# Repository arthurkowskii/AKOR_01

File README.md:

# AKOR_01

AKOR_01 is a compact hardware controller for playing notes, chords, and simple sequences.

These renders show the current NO_LED PCB revision: the RGB subsystem is absent, the matrix and encoder controls are routed, and the diode matrix is on the solder side.

The confirmed V0 interface contains a 4 × 5 performance grid plus Shift (21 MX switches total), seven push encoders, and an OLED display.

## Architecture locked on 2026-07-31

**V0 is an independent USB-MIDI controller based on Raspberry Pi Pico 2 H.**

A future standalone synthesizer is a separate V2 project. V2 is intentionally not a compatibility constraint for the V0 PCB.

### V0 hardware target

- Raspberry Pi Pico 2 H as the USB-MIDI device and control processor;
- 21 MX-compatible switches and 21 × 1N4148 in a scanned matrix;
- 7 bare EC11-style encoders with integrated push switches;
- 1 × MCP23017 I²C GPIO expander;
- 1 × SSD1306-compatible I²C OLED module;
- no onboard audio or DSP output stage.

The intended signal allocation is:

- encoder `A/B`: 14 direct Pico GPIO inputs;
- one encoder push switch: one direct Pico GPIO input;
- matrix rows/columns plus six encoder push switches: one MCP23017;
- OLED and MCP23017: shared 3.3 V I²C bus;
- USB: Pico 2 H onboard micro-USB, carrying power and class-compliant MIDI.

## Software state

The existing C++ prototype can:

- generate sine, square, triangle, and sawtooth waveforms;
- convert MIDI note numbers into frequencies;
- map a 16-key input across a chromatic octave range;
- apply an ADSR-style envelope;
- write mono 16-bit, 48 kHz WAV output.

That offline audio work is preserved for the separate V2. The V0 software goal is musical-state handling, control scanning, OLED feedback, and USB MIDI Note On/Off/Panic.

## Fabrication status

The NO_LED PCB layout has completed its routing and DRC checkpoint. It still requires a mechanical review and Gerber/NC Drill inspection before any fabrication order.

## Repository state (2026-08-08)

- `main` is the **single build source**: NO_LED V0 PCB (incl. MIDI DIN-5) + firmware.
- The RGB LED add-on work (SK6812MINI-E chain, 74AHCT1G125 buffer, associated SMD passives) is **archived, not part of V0**: see branch `archive/rgb-led` (commandes RGB, préservée). `archive/no-led-old` preserves the pre-DIN5 NO_LED branch (also deleted).
- `hardware/BOM_AKOR_01.csv` = buying/assembly list exported from Notion `Composants AKOR_01`, scoped to the NO_LED build only.

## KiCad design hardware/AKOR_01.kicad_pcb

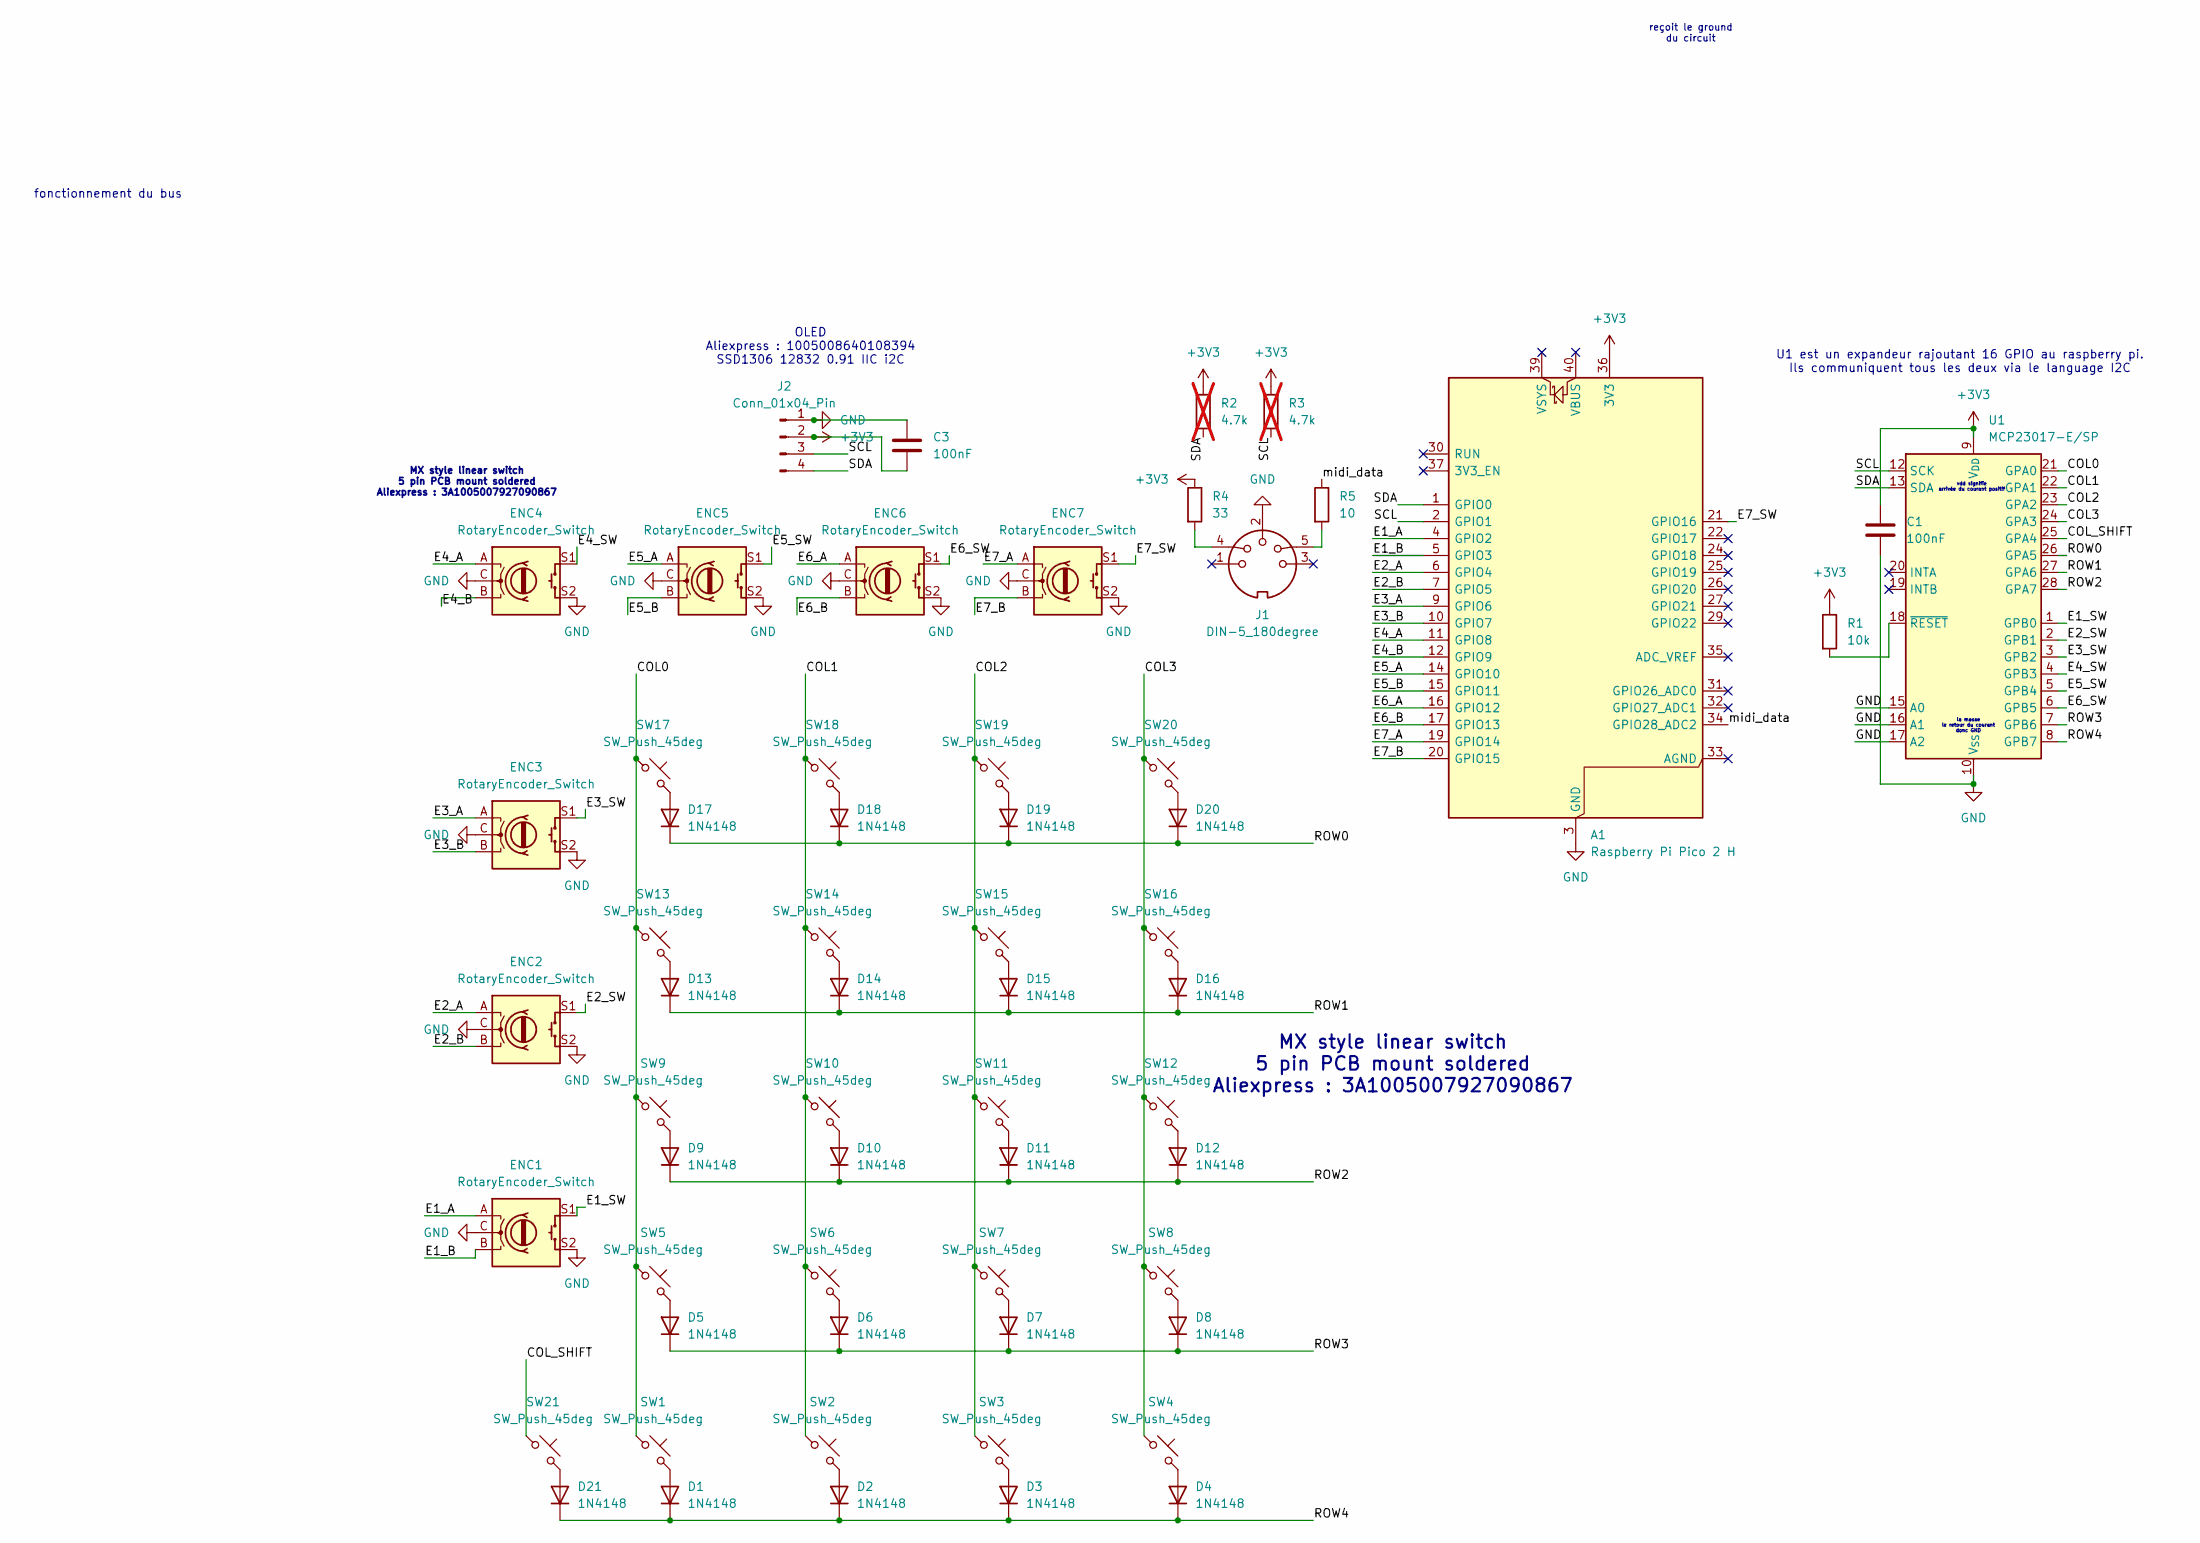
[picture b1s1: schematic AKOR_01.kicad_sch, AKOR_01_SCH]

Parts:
A1: Raspberry Pi Pico 2 H; RaspberryPi_Pico_Common_THT
C1, C3: 100nF; C_Disc_D5.0mm_W2.5mm_P5.00mm
D1, D2, D3, D4, D5, D6, D7, D8, D9, D10, D11, D12, D13, D14, D15, D16, D17, D18, D19, D20, D21: 1N4148; D_DO-35_SOD27_P10.16mm_Horizontal
ENC1, ENC2, ENC3, ENC4, ENC5, ENC6, ENC7: RotaryEncoder_Switch; RotaryEncoder_Alps_EC11E-Switch_Vertical_H20mm
J1: DIN-5_180degree; MIDI_DIN5
J2: Conn_01x04_Pin; ER_OLEDM0.91_1x-I2C
R1: 10k; R_Axial_DIN0207_L6.3mm_D2.5mm_P10.16mm_Horizontal
R2, R3: 4.7k; R_Axial_DIN0207_L6.3mm_D2.5mm_P10.16mm_Horizontal; not fitted
R4: 33; R_Axial_DIN0207_L6.3mm_D2.5mm_P10.16mm_Horizontal
R5: 10; R_Axial_DIN0207_L6.3mm_D2.5mm_P10.16mm_Horizontal
SW1, SW2, SW3, SW4, SW5, SW6, SW7, SW8, SW9, SW10, SW11, SW12, SW13, SW14, SW15, SW16, SW17, SW18, SW19, SW20, SW21: SW_Push_45deg; SW_Cherry_MX_1.00u_PCB
U1: MCP23017-E/SP; DIP-28_W7.62mm_Socket

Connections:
+3V3: A1.36 (3V3), C1.1, C3.2, J2.2, R1.1, R2.1, R3.1, R4.1, U1.9 (V_{DD})
/COL0: SW1.1, SW5.1, SW9.1, SW13.1, SW17.1, U1.21 (GPA0)
/COL1: SW2.1, SW6.1, SW10.1, SW14.1, SW18.1, U1.22 (GPA1)
/COL2: SW3.1, SW7.1, SW11.1, SW15.1, SW19.1, U1.23 (GPA2)
/COL3: SW4.1, SW8.1, SW12.1, SW16.1, SW20.1, U1.24 (GPA3)
/COL_SHIFT: SW21.1, U1.25 (GPA4)
/E1_A: A1.4 (GPIO2), ENC1.A
/E1_B: A1.5 (GPIO3), ENC1.B
/E1_SW: ENC1.S1, U1.1 (GPB0)
/E2_A: A1.6 (GPIO4), ENC2.A
/E2_B: A1.7 (GPIO5), ENC2.B
/E2_SW: ENC2.S1, U1.2 (GPB1)
/E3_A: A1.9 (GPIO6), ENC3.A
/E3_B: A1.10 (GPIO7), ENC3.B
/E3_SW: ENC3.S1, U1.3 (GPB2)
/E4_A: A1.11 (GPIO8), ENC4.A
/E4_B: A1.12 (GPIO9), ENC4.B
/E4_SW: ENC4.S1, U1.4 (GPB3)
/E5_A: A1.14 (GPIO10), ENC5.A
/E5_B: A1.15 (GPIO11), ENC5.B
/E5_SW: ENC5.S1, U1.5 (GPB4)
/E6_A: A1.16 (GPIO12), ENC6.A
/E6_B: A1.17 (GPIO13), ENC6.B
/E6_SW: ENC6.S1, U1.6 (GPB5)
/E7_A: A1.19 (GPIO14), ENC7.A
/E7_B: A1.20 (GPIO15), ENC7.B
/E7_SW: A1.21 (GPIO16), ENC7.S1
/ROW0: D17.1 (K), D18.1 (K), D19.1 (K), D20.1 (K), U1.26 (GPA5)
/ROW1: D13.1 (K), D14.1 (K), D15.1 (K), D16.1 (K), U1.27 (GPA6)
/ROW2: D9.1 (K), D10.1 (K), D11.1 (K), D12.1 (K), U1.28 (GPA7)
/ROW3: D5.1 (K), D6.1 (K), D7.1 (K), D8.1 (K), U1.7 (GPB6)
/ROW4: D1.1 (K), D2.1 (K), D3.1 (K), D4.1 (K), D21.1 (K), U1.8 (GPB7)
/SCL: A1.2 (GPIO1), J2.3, R3.2, U1.12 (SCK)
/SDA: A1.1 (GPIO0), J2.4, R2.2, U1.13 (SDA)
/midi_data: A1.34 (GPIO28_ADC2), R5.1
GND: A1.3 (GND), A1.8 (GND), A1.13 (GND), A1.18 (GND), A1.23 (GND), A1.28 (GND), A1.38 (GND), C1.2, C3.1, ENC1.C, ENC1.S2, ENC2.C, ENC2.S2, ENC3.C, ENC3.S2, ENC4.C, ENC4.S2, ENC5.C, ENC5.S2, ENC6.C, ENC6.S2, ENC7.C, ENC7.S2, J1.2, J2.1, U1.10 (V_{SS}), U1.15 (A0), U1.16 (A1), U1.17 (A2)
unnamed: D1.2 (A), SW1.2
unnamed: D2.2 (A), SW2.2
unnamed: D3.2 (A), SW3.2
unnamed: D4.2 (A), SW4.2
unnamed: D5.2 (A), SW5.2
unnamed: D6.2 (A), SW6.2
unnamed: D7.2 (A), SW7.2
unnamed: D8.2 (A), SW8.2
unnamed: D9.2 (A), SW9.2
unnamed: D10.2 (A), SW10.2
unnamed: D11.2 (A), SW11.2
unnamed: D12.2 (A), SW12.2
unnamed: D13.2 (A), SW13.2
unnamed: D14.2 (A), SW14.2
unnamed: D15.2 (A), SW15.2
unnamed: D16.2 (A), SW16.2
unnamed: D17.2 (A), SW17.2
unnamed: D18.2 (A), SW18.2
unnamed: D19.2 (A), SW19.2
unnamed: D20.2 (A), SW20.2
unnamed: D21.2 (A), SW21.2
unnamed: J1.4, R4.2
unnamed: J1.5, R5.2
unnamed: R1.2, U1.18 (~RESET)

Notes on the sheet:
la masse le retour du courant donc GND
vdd signifie arrivée du courant positif
MX style linear switch 5 pin PCB mount soldered Aliexpress : 3A1005007927090867
reçoit le ground du circuit
fonctionnement du bus
U1 est un expandeur rajoutant 16 GPIO au raspberry pi. Ils communiquent tous les deux via le language I2C
OLED Aliexpress : 1005008640108394 SSD1306 12832 0.91 IIC i2C

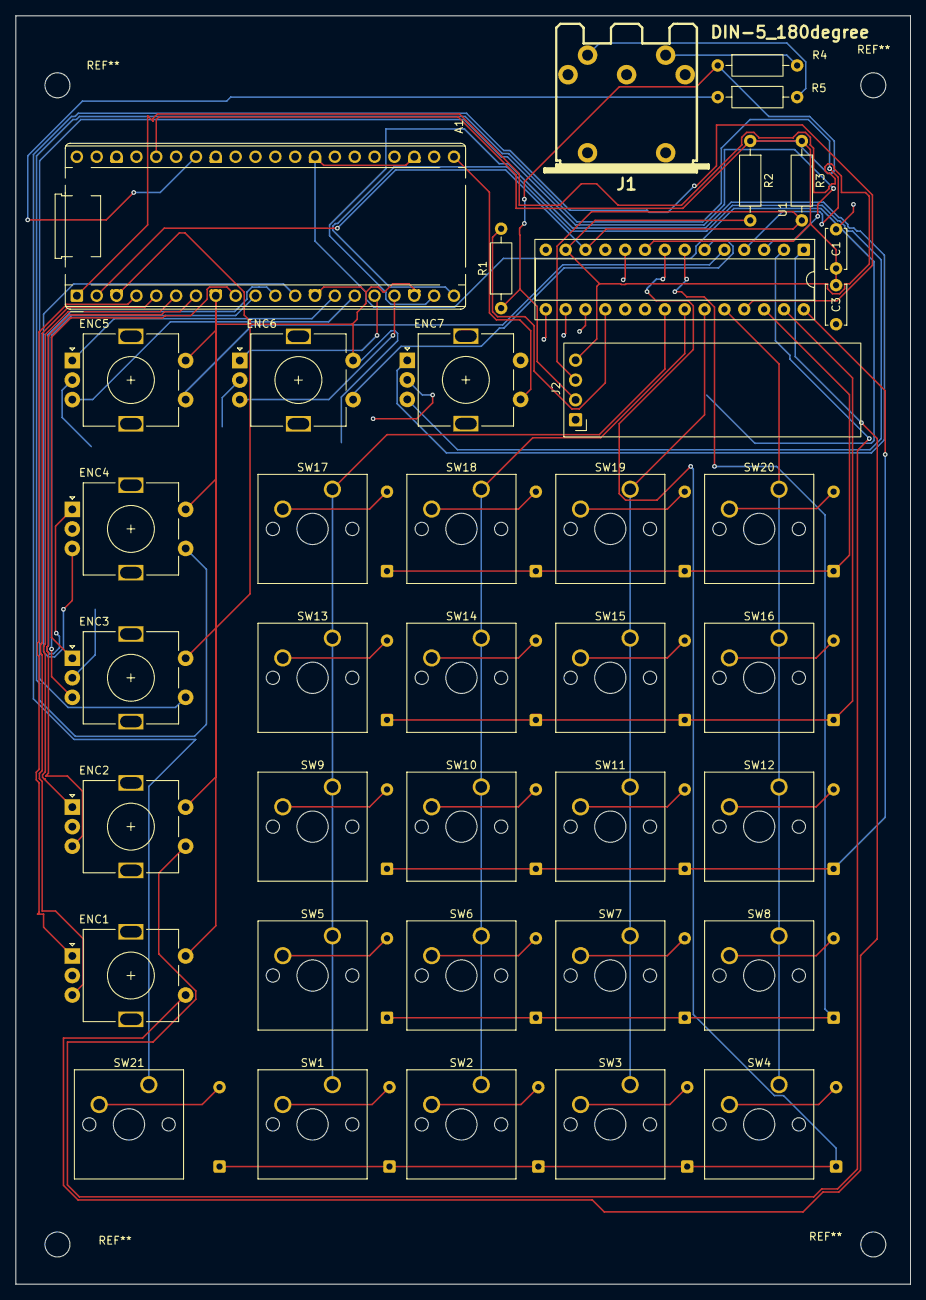
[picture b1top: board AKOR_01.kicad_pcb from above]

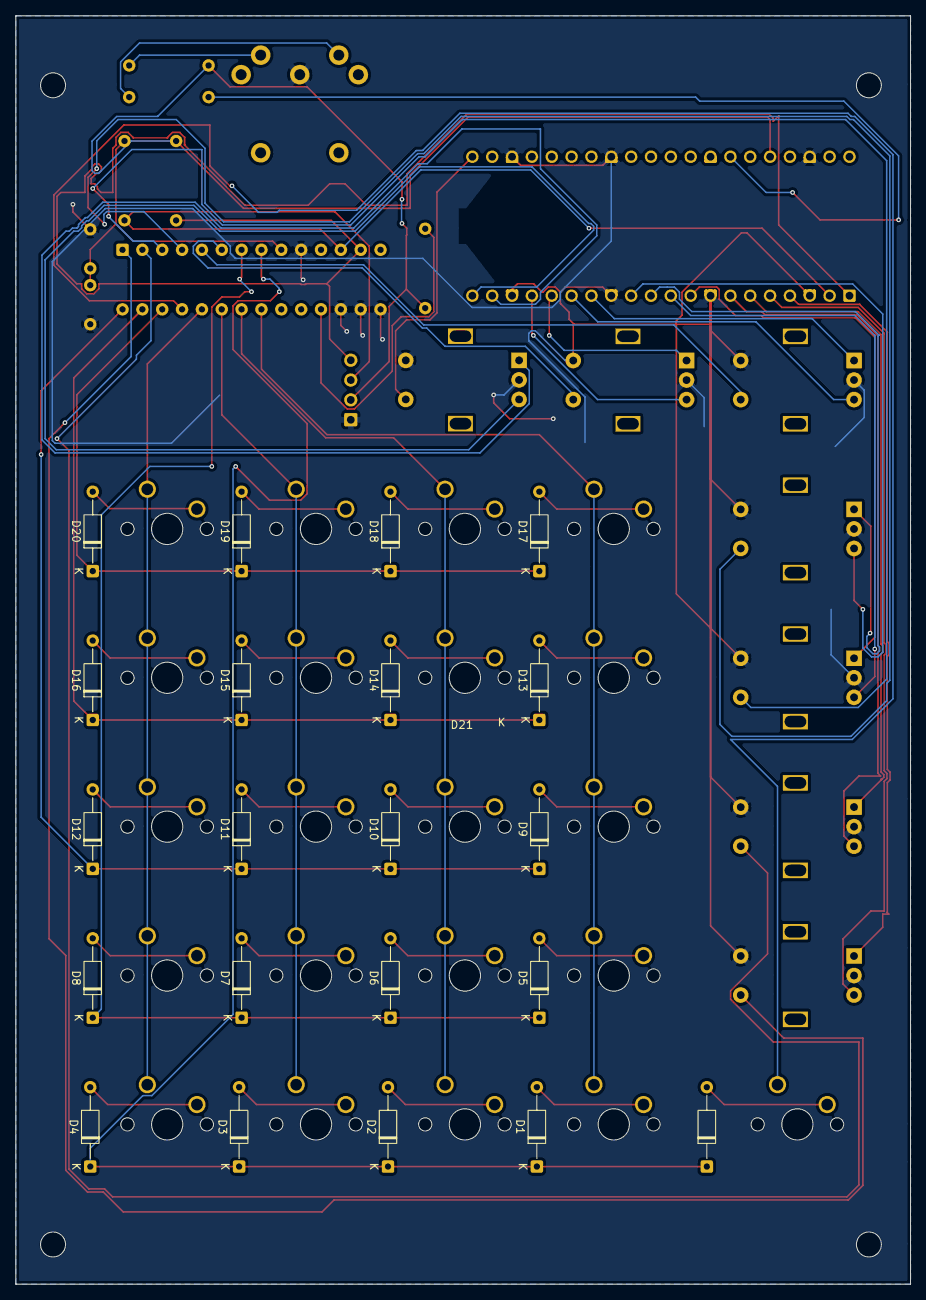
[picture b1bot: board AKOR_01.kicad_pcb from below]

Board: 2 copper layers, 114.5 x 162.3 mm, 60 parts (21 on the bottom side), 60 nets.
